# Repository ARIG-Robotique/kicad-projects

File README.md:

# Projets KiCAD de l'association ARIG

 ## Alimentation
 
 ### MasterAlim
 
 Module de contrôle I2C des alimentations et AU logique.

 ### ModuleAlim3A
 
 Module d'alimentation régulée 3A.

 ### ModuleAlim6A
 
 Module d'alimentation régulée 6A.

 ### ModuleMesure
 
 Module I2C de mesure tension/courant, 4 mesures.
 
 ### ModuleMesureDemi
 
 Module I2C de mesure tension/courant, 2 mesures.

 ## CapteursNumerique
 
 Module de lecture de 8 capteurs tout ou rien sur I2C.

 ## ControleursPompes
 
 Controle I2C de 4 pompes à vide + electrovannes + presiostats.

 ## InterfaceRaspi
 
 Shield Raspberry Pi pour connecter les modules.

 ## MultiplexeurCouleur
 
 Module de multiplexage I2C pour 8 capteurs de couleur.

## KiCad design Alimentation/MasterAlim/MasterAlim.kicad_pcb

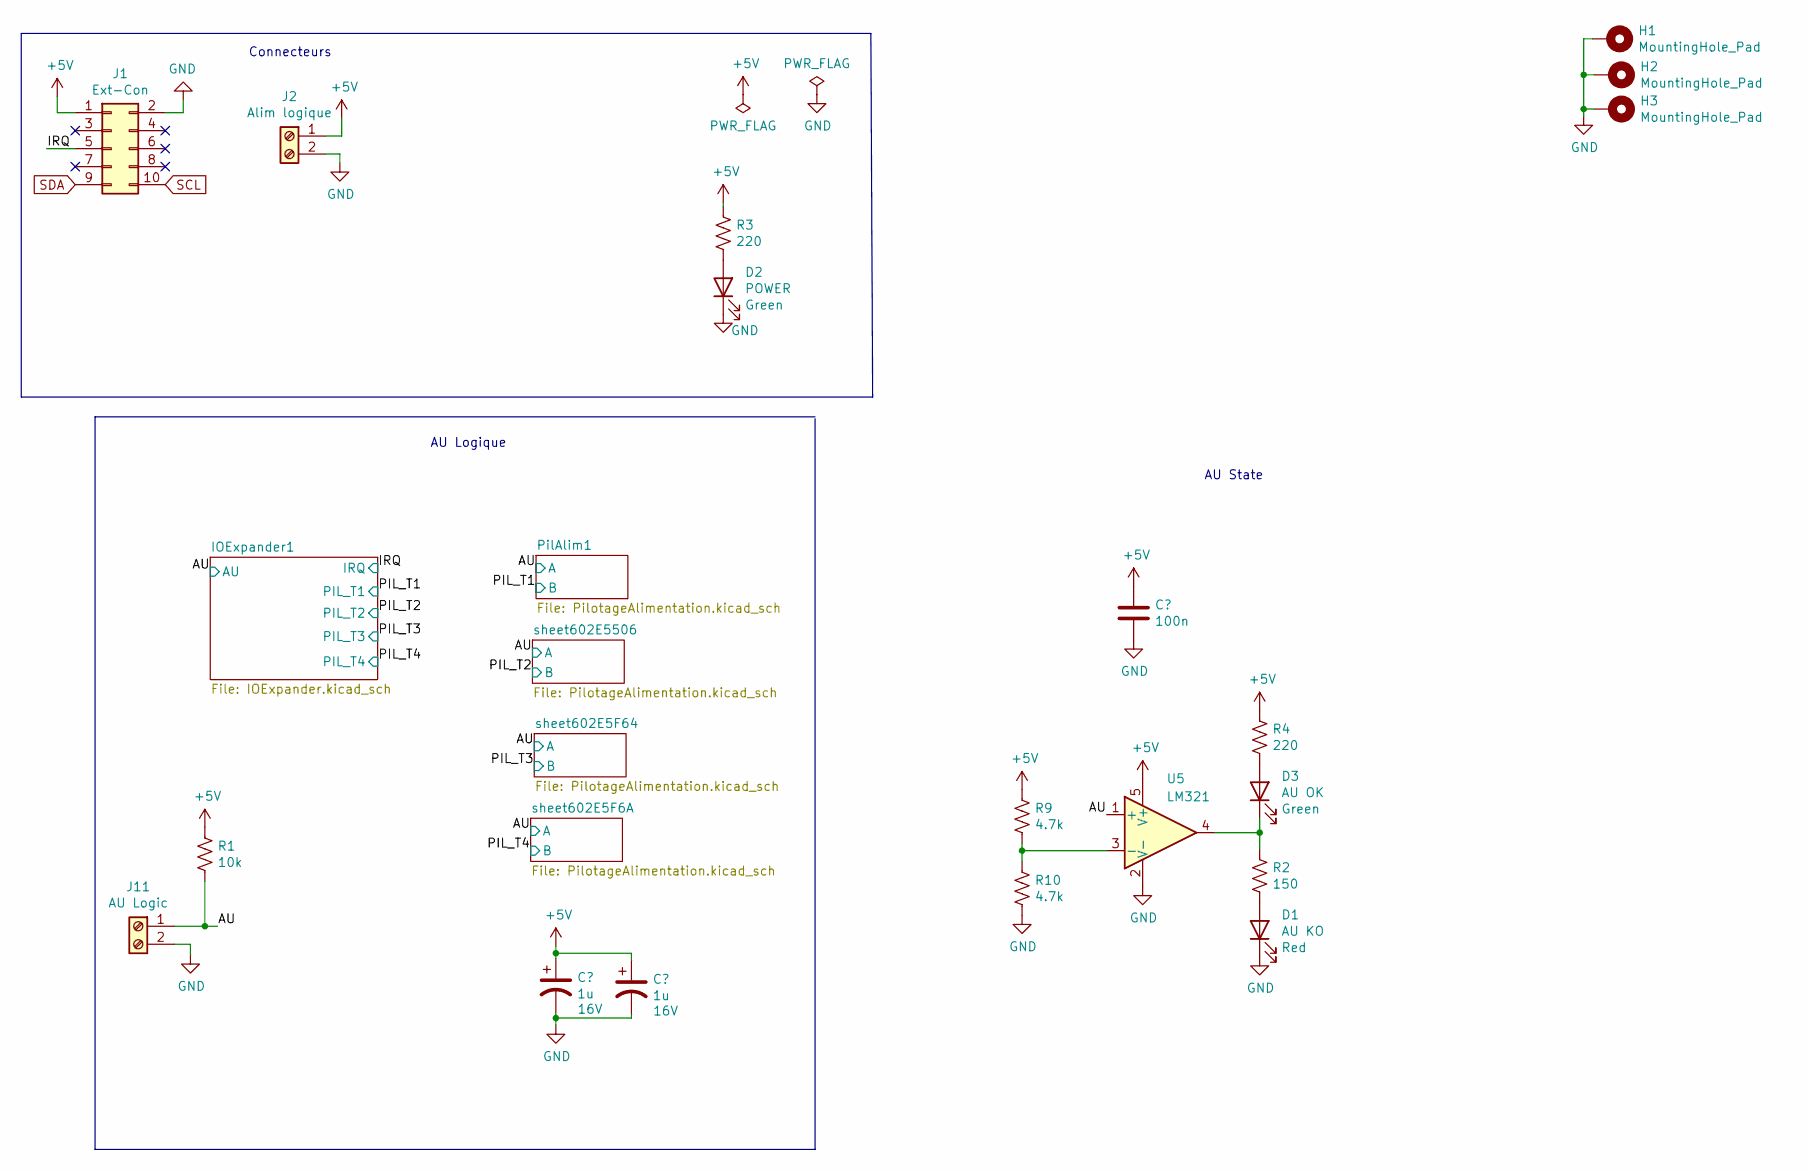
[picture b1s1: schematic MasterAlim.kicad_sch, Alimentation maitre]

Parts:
C1, C3: 1u; CP_Radial_D5.0mm_P2.50mm; JLCPCB BOM 0
C4: 100n; C_0603_1608Metric_Pad1.08x0.95mm_HandSolder; LCSC Part C14663
D1: AU KO; LED_0805_2012Metric; LCSC Part C72037
D2: POWER; LED_0805_2012Metric; LCSC Part C63855
D3: AU OK; LED_0805_2012Metric; LCSC Part C63855
H1, H2, H3: MountingHole_Pad; MountingHole_3.2mm_M3_Pad_Via; JLCPCB BOM 0
J1: Ext-Con; IDC-Header_2x05_P2.54mm_Vertical; JLCPCB BOM 0
J2: Alim logique; TerminalBlock_Phoenix_MKDS-1,5-2-5.08_1x02_P5.08mm_Horizont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; JLCPCB BOM 0
J11: AU Logic; TerminalBlock_Phoenix_MPT-0,5-2-2.54_1x02_P2.54mm_Horizontal; JLCPCB BOM 0
R1: 10k; R_0805_2012Metric_Pad1.20x1.40mm_HandSolder; LCSC Part C17414
R2: 150; R_0805_2012Metric_Pad1.20x1.40mm_HandSolder; LCSC Part C17471
R3, R4: 220; R_0805_2012Metric_Pad1.20x1.40mm_HandSolder; LCSC Part C17557
R9, R10: 4.7k; R_0805_2012Metric_Pad1.20x1.40mm_HandSolder
U5: LM321; SOT-23-5

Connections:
+5V: C1.1, C3.1, C4.1, J1.1, J2.1, R1.1, R3.1, R4.1, R9.1, U5.5 (V+); also elsewhere on the board
/AU: J11.1, R1.2, U5.1 (+); also elsewhere on the board
/IRQ: J1.5; also elsewhere on the board
GND: C1.2, C3.2, C4.2, D1.1 (K), D2.1 (K), H1.1, H2.1, H3.1, J1.2, J2.2, J11.2, R10.2, U5.2 (V-); also elsewhere on the board
unnamed: D1.2 (A), R2.2
unnamed: D2.2 (A), R3.2
unnamed: D3.1 (K), R2.1, U5.4
unnamed: D3.2 (A), R4.2
unnamed: R9.2, R10.1, U5.3 (-)
SCL: J1.10; also elsewhere on the board
SDA: J1.9; also elsewhere on the board

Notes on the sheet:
Connecteurs
AU Logique
AU State

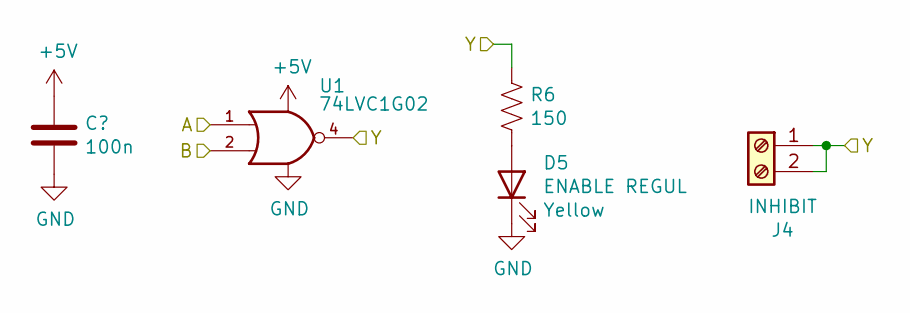
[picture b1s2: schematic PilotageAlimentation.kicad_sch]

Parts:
C6: 100n; C_0603_1608Metric_Pad1.08x0.95mm_HandSolder; LCSC Part C14663
D5: ENABLE REGUL; LED_0805_2012Metric; LCSC Part C74346
J4: INHIBIT; TerminalBlock_Phoenix_MPT-0,5-2-2.54_1x02_P2.54mm_Horizontal; JLCPCB BOM 0
R6: 150; R_0805_2012Metric_Pad1.20x1.40mm_HandSolder; LCSC Part C17471
U1: 74LVC1G02; SOT-23-5_HandSoldering; LCSC Part C16360

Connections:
+5V: C6.1, U1.5 (VCC); also elsewhere on the board
/AU: U1.1; also elsewhere on the board
/PIL_T1: U1.2; also elsewhere on the board
GND: C6.2, D5.1 (K), U1.3 (GND); also elsewhere on the board
unnamed: D5.2 (A), R6.2

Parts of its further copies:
C2, C8, C10: 100n; C_0603_1608Metric_Pad1.08x0.95mm_HandSolder; LCSC Part C14663
D4, D6, D8: ENABLE REGUL; LED_0805_2012Metric; LCSC Part C74346
J6, J8, J12: INHIBIT; TerminalBlock_Phoenix_MPT-0,5-2-2.54_1x02_P2.54mm_Horizontal; JLCPCB BOM 0
R5, R7, R8: 150; R_0805_2012Metric_Pad1.20x1.40mm_HandSolder; LCSC Part C17471
U2, U3, U4: 74LVC1G02; SOT-23-5_HandSoldering; LCSC Part C16360

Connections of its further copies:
+5V: C2.1, C8.1, C10.1, U2.5 (VCC), U3.5 (VCC), U4.5 (VCC); also elsewhere on the board
/AU: U2.1, U3.1, U4.1; also elsewhere on the board
/PIL_T2: U2.2; also elsewhere on the board
/PIL_T3: U3.2; also elsewhere on the board
/PIL_T4: U4.2; also elsewhere on the board
/sheet602E5F6A/Y: J12.1, J12.2, R8.1, U4.4
/sheet602E5F64/Y: J8.1, J8.2, R7.1, U3.4
GND: C2.2, C8.2, C10.2, D4.1 (K), D6.1 (K), D8.1 (K), U2.3 (GND), U3.3 (GND), U4.3 (GND); also elsewhere on the board
unnamed: D4.2 (A), R5.2
unnamed: D6.2 (A), R7.2
unnamed: D8.2 (A), R8.2

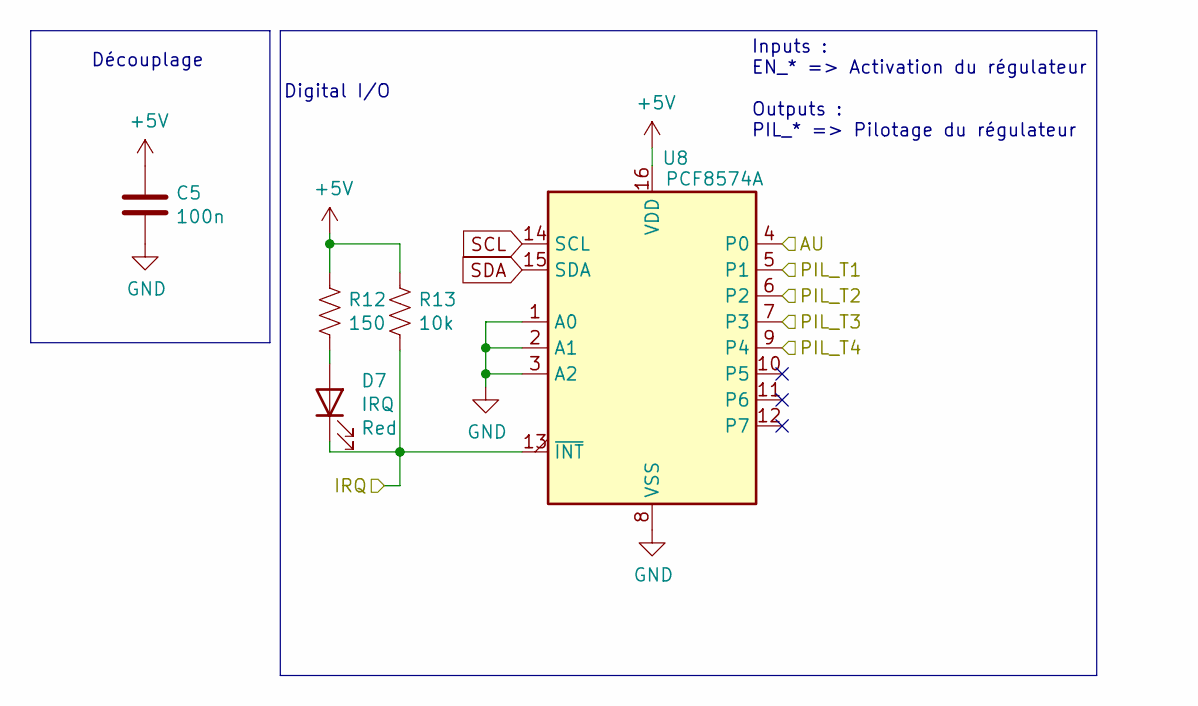
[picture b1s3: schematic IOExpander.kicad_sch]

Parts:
C5: 100n; C_0603_1608Metric_Pad1.08x0.95mm_HandSolder; LCSC Part C14663
D7: IRQ; LED_0805_2012Metric; LCSC Part C72037
R12: 150; R_0805_2012Metric_Pad1.20x1.40mm_HandSolder; LCSC Part C17471
R13: 10k; R_0805_2012Metric_Pad1.20x1.40mm_HandSolder; LCSC Part C17414
U8: PCF8574A; SOIC-16W_7.5x10.3mm_P1.27mm; LCSC Part C86832

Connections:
+5V: C5.1, R12.1, R13.1, U8.16 (VDD); also elsewhere on the board
/AU: U8.4 (P0); also elsewhere on the board
/IRQ: D7.1 (K), R13.2, U8.13 (~INT); also elsewhere on the board
/PIL_T1: U8.5 (P1); also elsewhere on the board
/PIL_T2: U8.6 (P2); also elsewhere on the board
/PIL_T3: U8.7 (P3); also elsewhere on the board
/PIL_T4: U8.9 (P4); also elsewhere on the board
GND: C5.2, U8.1 (A0), U8.2 (A1), U8.3 (A2), U8.8 (VSS); also elsewhere on the board
unnamed: D7.2 (A), R12.2
SCL: U8.14 (SCL); also elsewhere on the board
SDA: U8.15 (SDA); also elsewhere on the board

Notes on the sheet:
Digital I/O
Inputs : EN_* => Activation du régulateur Outputs : PIL_* => Pilotage du régulateur
Découplage

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
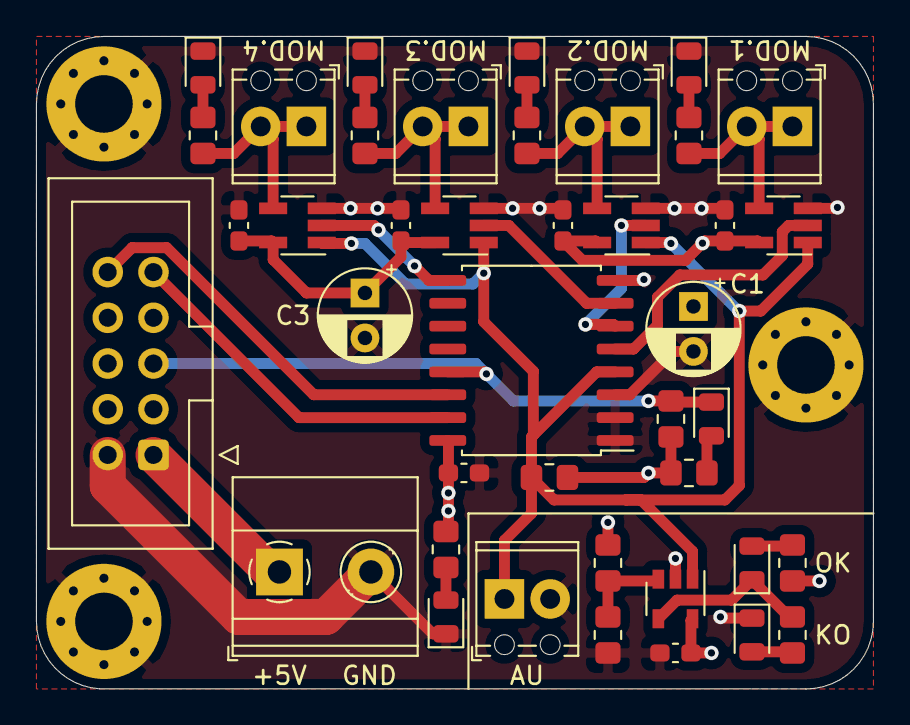
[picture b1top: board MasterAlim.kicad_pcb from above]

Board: 4 copper layers, 46.5 x 36.2 mm, 44 parts (0 on the bottom side), 24 nets.

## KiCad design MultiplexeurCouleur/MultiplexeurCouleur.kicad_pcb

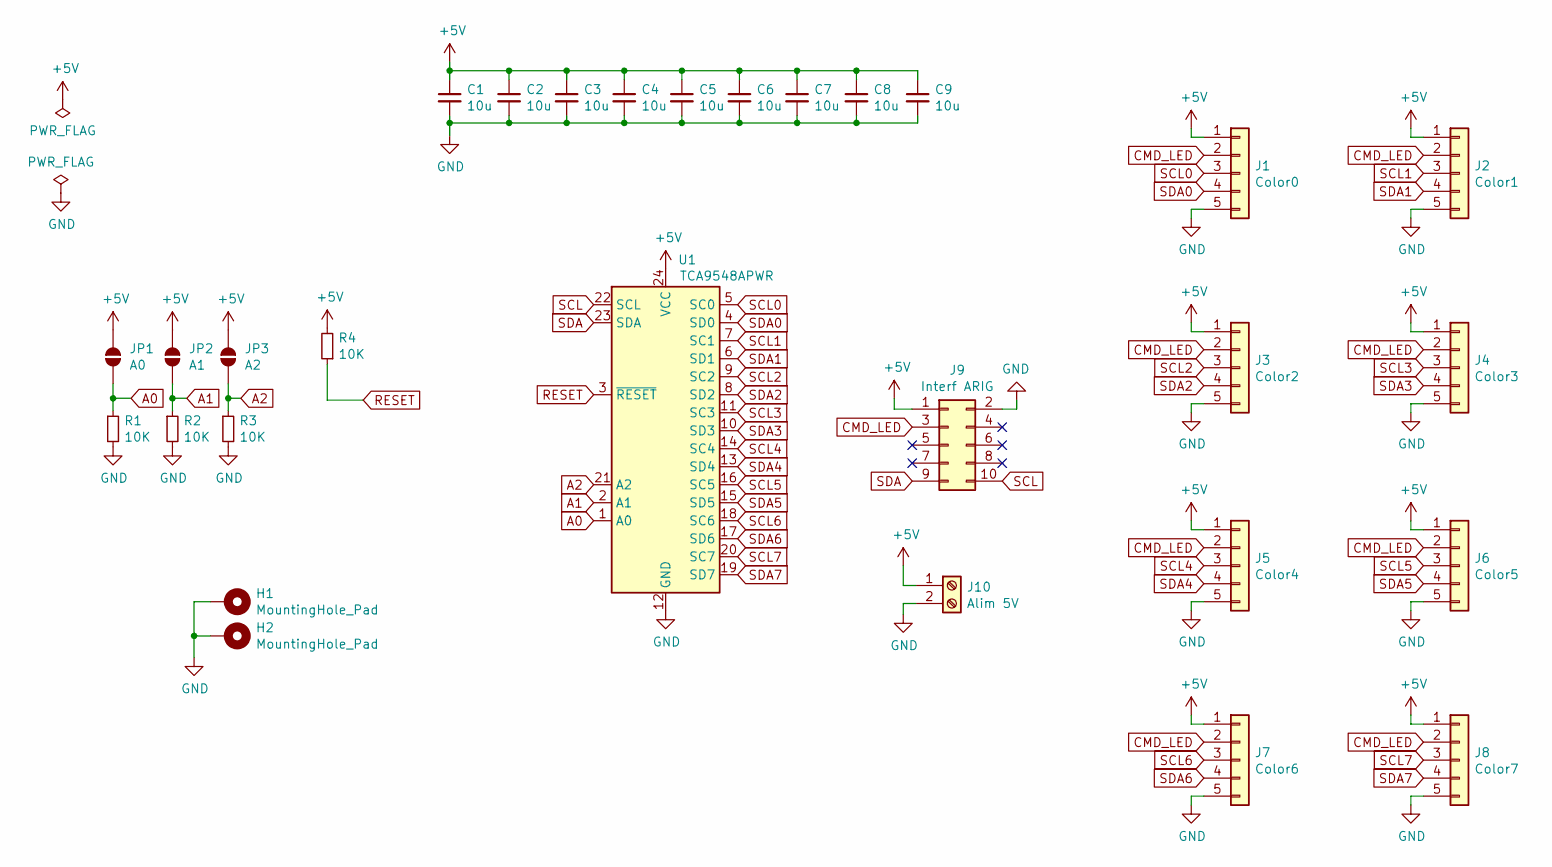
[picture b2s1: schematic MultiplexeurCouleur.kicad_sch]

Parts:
C1, C2, C3, C4, C5, C6, C7, C8, C9: 10u; C_0805_2012Metric_Pad1.18x1.45mm_HandSolder; LCSC Part C15850
H1, H2: MountingHole_Pad; MountingHole_3.2mm_M3_Pad_Via; JLCPCB BOM 0
J1: Color0; JST_PH_B5B-PH-K_1x05_P2.00mm_Vertical; JLCPCB BOM 0
J2: Color1; JST_PH_B5B-PH-K_1x05_P2.00mm_Vertical; JLCPCB BOM 0
J3: Color2; JST_PH_B5B-PH-K_1x05_P2.00mm_Vertical; JLCPCB BOM 0
J4: Color3; JST_PH_B5B-PH-K_1x05_P2.00mm_Vertical; JLCPCB BOM 0
J5: Color4; JST_PH_B5B-PH-K_1x05_P2.00mm_Vertical; JLCPCB BOM 0
J6: Color5; JST_PH_B5B-PH-K_1x05_P2.00mm_Vertical; JLCPCB BOM 0
J7: Color6; JST_PH_B5B-PH-K_1x05_P2.00mm_Vertical; JLCPCB BOM 0
J8: Color7; JST_PH_B5B-PH-K_1x05_P2.00mm_Vertical; JLCPCB BOM 0
J9: Interf ARIG; IDC-Header_2x05_P2.54mm_Vertical; JLCPCB BOM 0
J10: Alim 5V; TerminalBlock_Phoenix_MPT-0,5-2-2.54_1x02_P2.54mm_Horizontal; JLCPCB BOM 0
JP1: A0; SolderJumper-2_P1.3mm_Open_Pad1.0x1.5mm; JLCPCB BOM 0
JP2: A1; SolderJumper-2_P1.3mm_Open_Pad1.0x1.5mm; JLCPCB BOM 0
JP3: A2; SolderJumper-2_P1.3mm_Open_Pad1.0x1.5mm; JLCPCB BOM 0
R1, R2, R3, R4: 10K; R_0805_2012Metric_Pad1.20x1.40mm_HandSolder; LCSC Part C17414
U1: TCA9548APWR; TSSOP-24_4.4x7.8mm_P0.65mm; LCSC Part C130026

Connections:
+5V: C1.1, C2.1, C3.1, C4.1, C5.1, C6.1, C7.1, C8.1, C9.1, J1.1, J2.1, J3.1, J4.1, J5.1, J6.1, J7.1, J8.1, J9.1, J10.1, JP1.2 (B), JP2.2 (B), JP3.2 (B), R4.2, U1.24 (VCC)
A0: JP1.1 (A), R1.1, U1.1 (A0)
A1: JP2.1 (A), R2.1, U1.2 (A1)
A2: JP3.1 (A), R3.1, U1.21 (A2)
CMD_LED: J1.2, J2.2, J3.2, J4.2, J5.2, J6.2, J7.2, J8.2, J9.3
GND: C1.2, C2.2, C3.2, C4.2, C5.2, C6.2, C7.2, C8.2, C9.2, H1.1, H2.1, J1.5, J2.5, J3.5, J4.5, J5.5, J6.5, J7.5, J8.5, J9.2, J10.2, R1.2, R2.2, R3.2, U1.12 (GND)
RESET: R4.1, U1.3 (~RESET)
SCL: J9.10, U1.22 (SCL)
SCL0: J1.3, U1.5 (SC0)
SCL1: J2.3, U1.7 (SC1)
SCL2: J3.3, U1.9 (SC2)
SCL3: J4.3, U1.11 (SC3)
SCL4: J5.3, U1.14 (SC4)
SCL5: J6.3, U1.16 (SC5)
SCL6: J7.3, U1.18 (SC6)
SCL7: J8.3, U1.20 (SC7)
SDA: J9.9, U1.23 (SDA)
SDA0: J1.4, U1.4 (SD0)
SDA1: J2.4, U1.6 (SD1)
SDA2: J3.4, U1.8 (SD2)
SDA3: J4.4, U1.10 (SD3)
SDA4: J5.4, U1.13 (SD4)
SDA5: J6.4, U1.15 (SD5)
SDA6: J7.4, U1.17 (SD6)
SDA7: J8.4, U1.19 (SD7)

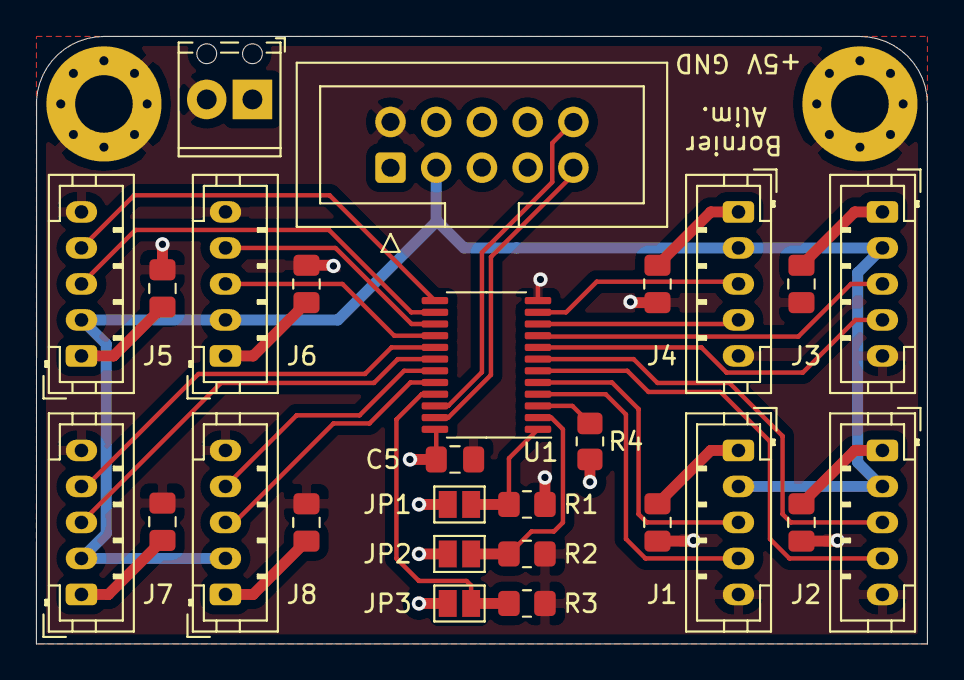
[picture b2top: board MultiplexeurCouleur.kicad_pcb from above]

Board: 4 copper layers, 49.5 x 33.8 mm, 29 parts (0 on the bottom side), 25 nets.

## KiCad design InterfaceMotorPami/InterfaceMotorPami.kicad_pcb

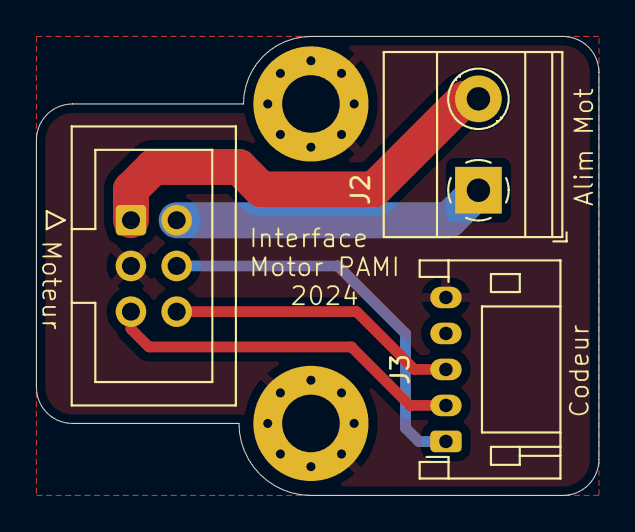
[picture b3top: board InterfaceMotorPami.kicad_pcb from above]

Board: 2 copper layers, 31.3 x 25.5 mm, 5 parts (0 on the bottom side), 6 nets.

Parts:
H1, H2: MountingHole_Pad; MountingHole_3.2mm_M3_Pad_Via
J1: MOT; IDC-Header_2x03_P2.54mm_Vertical
J2: PONT H; TerminalBlock_Phoenix_MKDS-1,5-2-5.08_1x02_P5.08mm_Horizont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
J3: Codeur; JST_PH_S5B-PH-K_1x05_P2.00mm_Horizontal

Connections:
+5V: J1.4, J3.1
/CHA: J1.5, J3.2
/CHB: J1.6, J3.3
/MOT+: J1.2, J2.1
/MOT-: J1.1, J2.2
GND: H1.1, H2.1, J1.3, J3.5

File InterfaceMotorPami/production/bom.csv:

Designator,Footprint,Quantity,Value,LCSC Part #
"H1, H2",MountingHole_3.2mm_M3_Pad_Via,2,MountingHole_Pad,
J1,IDC-Header_2x03_P2.54mm_Vertical,1,MOT,
J2,"TerminalBlock_Phoenix_MKDS-1,5-2-5.08_1x02_P5.08mm_Horizontal",1,PONT H,
J3,JST_PH_S5B-PH-K_1x05_P2.00mm_Horizontal,1,Codeur,

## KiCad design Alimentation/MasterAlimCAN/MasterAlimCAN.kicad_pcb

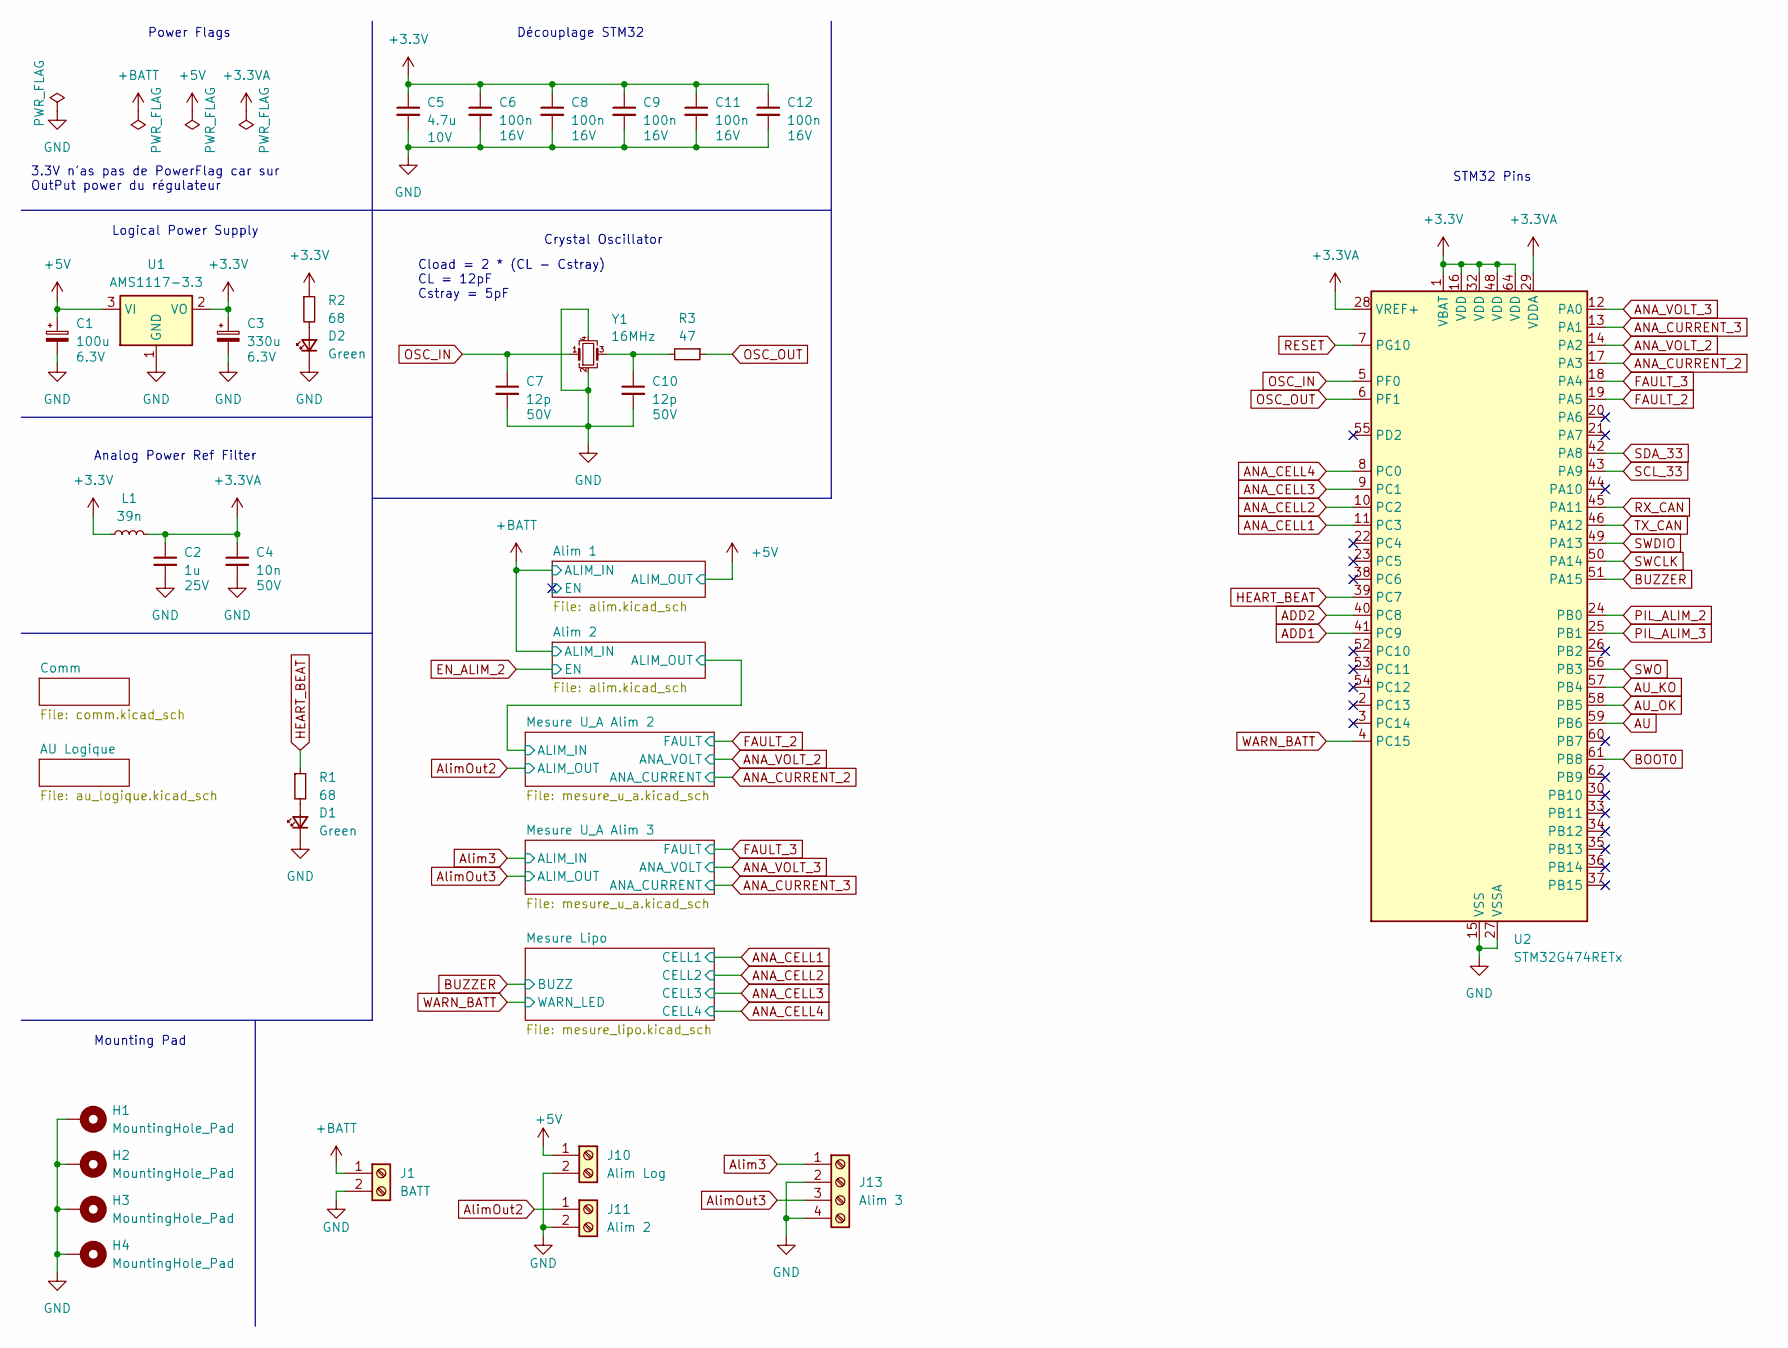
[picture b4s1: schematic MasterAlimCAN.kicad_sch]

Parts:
C1: 100u; CP_Elec_5x5.3; LCSC Part C249463
C2: 1u; C_0402_1005Metric_Pad0.74x0.62mm_HandSolder; LCSC Part C52923
C3: 330u; CP_Elec_6.3x7.7; LCSC Part C249900
C4: 10n; C_0402_1005Metric_Pad0.74x0.62mm_HandSolder; LCSC Part C15195
C5: 4.7u; C_0402_1005Metric_Pad0.74x0.62mm_HandSolder; LCSC Part C23733
C6, C8, C9, C11, C12: 100n; C_0402_1005Metric_Pad0.74x0.62mm_HandSolder; LCSC Part C1525
C7, C10: 12p; C_0402_1005Metric_Pad0.74x0.62mm_HandSolder; LCSC Part C1547
D1, D2: Green; LED_0805_2012Metric_Pad1.15x1.40mm_HandSolder; LCSC Part C63855
H1, H2, H3, H4: MountingHole_Pad; MountingHole_3.2mm_M3_Pad_Via; JLCPCB BOM 0
J1: BATT; TerminalBlock_Phoenix_MKDS-1,5-2-5.08_1x02_P5.08mm_Horizont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; JLCPCB BOM 0
J10: Alim Log; TerminalBlock_Phoenix_MKDS-1,5-2-5.08_1x02_P5.08mm_Horizont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; JLCPCB BOM 0
J11: Alim 2; TerminalBlock_Phoenix_MKDS-1,5-2-5.08_1x02_P5.08mm_Horizont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; JLCPCB BOM 0
J13: Alim 3; TerminalBlock_Phoenix_MKDS-1,5-4-5.08_1x04_P5.08mm_Horizont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; JLCPCB BOM 0
L1: 39n; L_0402_1005Metric_Pad0.77x0.64mm_HandSolder; LCSC Part C26443
R1, R2: 68; R_0805_2012Metric_Pad1.20x1.40mm_HandSolder; LCSC Part C17802
R3: 47; R_0402_1005Metric_Pad0.72x0.64mm_HandSolder; LCSC Part C25118
U1: AMS1117-3.3; SOT-223-3_TabPin2; LCSC Part C6186
U2: STM32G474RETx; LQFP-64_10x10mm_P0.5mm; LCSC Part C521608
Y1: 16MHz; Crystal_SMD_3225-4Pin_3.2x2.5mm_HandSoldering; LCSC Part C13738

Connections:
+3.3V: C3.1, C5.1, C6.1, C8.1, C9.1, C11.1, C12.1, L1.1, R2.1, U1.2 (VO), U2.1 (VBAT), U2.16 (VDD), U2.32 (VDD), U2.48 (VDD), U2.64 (VDD); also elsewhere on the board
+3.3VA: C2.1, C4.1, L1.2, U2.28 (VREF+), U2.29 (VDDA)
+5V: C1.1, J10.1, U1.3 (VI); also elsewhere on the board
+BATT: J1.1; also elsewhere on the board
ADD1: U2.41 (PC9); also elsewhere on the board
ADD2: U2.40 (PC8); also elsewhere on the board
ANA_CELL1: U2.11 (PC3); also elsewhere on the board
ANA_CELL2: U2.10 (PC2); also elsewhere on the board
ANA_CELL3: U2.9 (PC1); also elsewhere on the board
ANA_CELL4: U2.8 (PC0); also elsewhere on the board
ANA_CURRENT_2: U2.17 (PA3); also elsewhere on the board
ANA_CURRENT_3: U2.13 (PA1); also elsewhere on the board
ANA_VOLT_2: U2.14 (PA2); also elsewhere on the board
ANA_VOLT_3: U2.12 (PA0); also elsewhere on the board
AU: U2.59 (PB6); also elsewhere on the board
AU_KO: U2.57 (PB4); also elsewhere on the board
AU_OK: U2.58 (PB5); also elsewhere on the board
AlimOut2: J11.1; also elsewhere on the board
AlimOut3: J13.3; also elsewhere on the board
BOOT0: U2.61 (PB8); also elsewhere on the board
BUZZER: U2.51 (PA15); also elsewhere on the board
GND: C1.2, C2.2, C3.2, C4.2, C5.2, C6.2, C7.2, C8.2, C9.2, C10.2, C11.2, C12.2, D1.1 (K), D2.1 (K), H1.1, H2.1, H3.1, H4.1, J1.2, J10.2, J11.2, J13.2, J13.4, U1.1 (GND), U2.15 (VSS), U2.27 (VSSA), U2.31 (VSS), U2.47 (VSS), U2.63 (VSS), Y1.2, Y1.4; also elsewhere on the board
HEART_BEAT: R1.1, U2.39 (PC7)
unnamed: C10.1, R3.2, Y1.3
unnamed: D1.2 (A), R1.2
unnamed: D2.2 (A), R2.2
OSC_IN: C7.1, U2.5 (PF0), Y1.1
OSC_OUT: R3.1, U2.6 (PF1)
PIL_ALIM_2: U2.24 (PB0); also elsewhere on the board
PIL_ALIM_3: U2.25 (PB1); also elsewhere on the board
RESET: U2.7 (PG10); also elsewhere on the board
RX_CAN: U2.45 (PA11); also elsewhere on the board
SCL_33: U2.43 (PA9); also elsewhere on the board
SDA_33: U2.42 (PA8); also elsewhere on the board
SWCLK: U2.50 (PA14); also elsewhere on the board
SWDIO: U2.49 (PA13); also elsewhere on the board
SWO: U2.56 (PB3); also elsewhere on the board
TX_CAN: U2.46 (PA12); also elsewhere on the board
WARN_BATT: U2.4 (PC15); also elsewhere on the board

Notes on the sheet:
Analog Power Ref Filter
STM32 Pins
Mounting Pad
Crystal Oscillator
3.3V n'as pas de PowerFlag car sur OutPut power du régulateur
Découplage STM32
Power Flags
Logical Power Supply
Cload = 2 * (CL - Cstray) CL = 12pF Cstray = 5pF

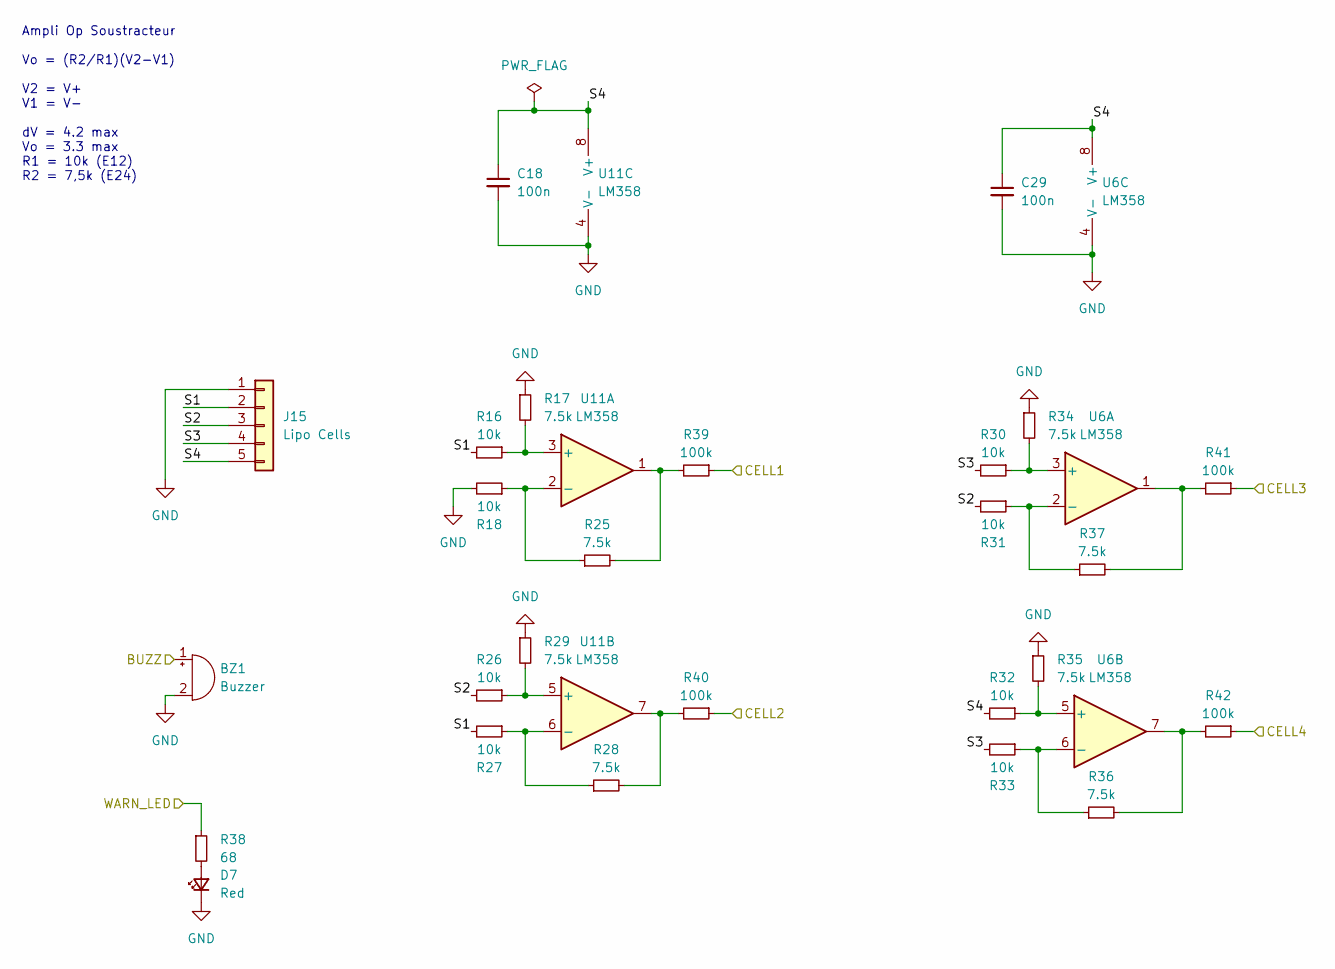
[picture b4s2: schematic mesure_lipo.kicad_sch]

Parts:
BZ1: Buzzer; MagneticBuzzer_CUI_CST-931RP-A; JLCPCB BOM 0
C18, C29: 100n; C_0402_1005Metric_Pad0.74x0.62mm_HandSolder; LCSC Part C100072
D7: Red; LED_0805_2012Metric_Pad1.15x1.40mm_HandSolder; LCSC Part C72037
J15: Lipo Cells; JST_PH_S5B-PH-K_1x05_P2.00mm_Horizontal; JLCPCB BOM 0
R16, R18, R26, R27, R30, R31, R32, R33: 10k; R_0805_2012Metric_Pad1.20x1.40mm_HandSolder; LCSC Part C17414
R17, R25, R28, R29, R34, R35, R36, R37: 7.5k; R_0805_2012Metric_Pad1.20x1.40mm_HandSolder; LCSC Part C17807
R38: 68; R_0805_2012Metric_Pad1.20x1.40mm_HandSolder; LCSC Part C17802
R39, R40, R41, R42: 100k; R_0805_2012Metric_Pad1.20x1.40mm_HandSolder; LCSC Part C25611
U6, U11: LM358; SO-8_3.9x4.9mm_P1.27mm; LCSC Part C9418

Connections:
/Mesure Lipo/S1: J15.2, R16.2, R27.2
/Mesure Lipo/S2: J15.3, R26.2, R31.2
/Mesure Lipo/S3: J15.4, R30.2, R33.2
/Mesure Lipo/S4: C18.1, C29.1, J15.5, R32.2, U6.8 (V+), U11.8 (V+)
ANA_CELL1: R39.1; also elsewhere on the board
ANA_CELL2: R40.1; also elsewhere on the board
ANA_CELL3: R41.1; also elsewhere on the board
ANA_CELL4: R42.1; also elsewhere on the board
BUZZER: BZ1.1 (+); also elsewhere on the board
GND: BZ1.2 (-), C18.2, C29.2, D7.1 (K), J15.1, R17.1, R18.2, R29.1, R34.1, R35.1, U6.4 (V-), U11.4 (V-); also elsewhere on the board
unnamed: D7.2 (A), R38.2
unnamed: R25.2, R39.2, U11.1
unnamed: R28.2, R40.2, U11.7
unnamed: R36.2, R42.2, U6.7
unnamed: R37.2, R41.2, U6.1
unnamed: R30.1, R34.2, U6.3 (+)
unnamed: R31.1, R37.1, U6.2 (-)
unnamed: R32.1, R35.2, U6.5 (+)
unnamed: R33.1, R36.1, U6.6 (-)
unnamed: R16.1, R17.2, U11.3 (+)
unnamed: R18.1, R25.1, U11.2 (-)
unnamed: R26.1, R29.2, U11.5 (+)
unnamed: R27.1, R28.1, U11.6 (-)
WARN_BATT: R38.1; also elsewhere on the board

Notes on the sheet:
Ampli Op Soustracteur Vo = (R2/R1)(V2-V1) V2 = V+ V1 = V- dV = 4.2 max Vo = 3.3 max R1 = 10k (E12) R2 = 7,5k (E24)

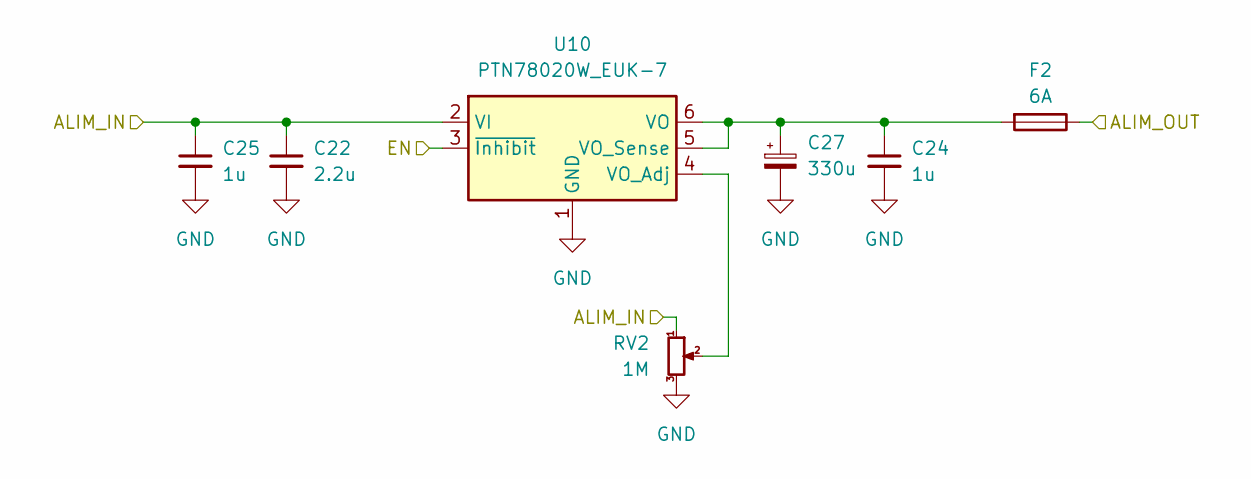
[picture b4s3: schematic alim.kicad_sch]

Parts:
C22: 2.2u; C_1206_3216Metric_Pad1.33x1.80mm_HandSolder; LCSC Part C50254
C24: 1u; C_0402_1005Metric_Pad0.74x0.62mm_HandSolder; LCSC Part C52923
C25: 1u; C_0805_2012Metric_Pad1.18x1.45mm_HandSolder; LCSC Part C28323
C27: 330u; CP_Elec_8x10; LCSC Part C134842
F2: 6A; Fuseholder_Cylinder-5x20mm_Schurter_0031_8201_Horizontal_Op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; JLCPCB BOM 0
RV2: 1M; Potentiometer_Bourns_3266Y_Vertical; JLCPCB BOM 0
U10: PTN78020W_EUK-7; Texas_EUK_R-PDSS-T7_THT; LCSC Part C5219636

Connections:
+BATT: C22.1, C25.1, RV2.1, U10.2 (VI); also elsewhere on the board
EN_ALIM_2: U10.3 (~Inhibit); also elsewhere on the board
GND: C22.2, C24.2, C25.2, C27.2, RV2.3, U10.1 (GND), U10.7 (GND); also elsewhere on the board
unnamed: RV2.2, U10.4 (VO_Adj)

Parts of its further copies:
C21: 1u; C_0805_2012Metric_Pad1.18x1.45mm_HandSolder; LCSC Part C28323
C23: 330u; CP_Elec_8x10; LCSC Part C134842
C26: 2.2u; C_1206_3216Metric_Pad1.33x1.80mm_HandSolder; LCSC Part C50254
C28: 1u; C_0402_1005Metric_Pad0.74x0.62mm_HandSolder; LCSC Part C52923
F1: 6A; Fuseholder_Cylinder-5x20mm_Schurter_0031_8201_Horizontal_Op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; JLCPCB BOM 0
RV1: 1M; Potentiometer_Bourns_3266Y_Vertical; JLCPCB BOM 0
U9: PTN78020W_EUK-7; Texas_EUK_R-PDSS-T7_THT; LCSC Part C5219636

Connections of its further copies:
+5V: F1.1; also elsewhere on the board
+BATT: C21.1, C26.1, RV1.1, U9.2 (VI); also elsewhere on the board
/Alim 1/EN: U9.3 (~Inhibit)
GND: C21.2, C23.2, C26.2, C28.2, RV1.3, U9.1 (GND), U9.7 (GND); also elsewhere on the board
unnamed: RV1.2, U9.4 (VO_Adj)

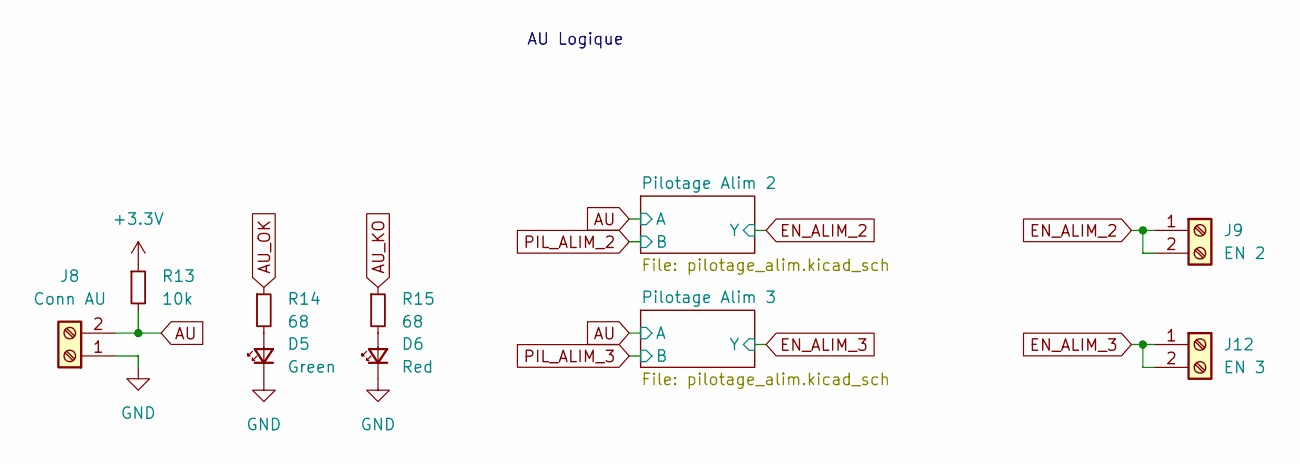
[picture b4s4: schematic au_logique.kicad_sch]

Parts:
D5: Green; LED_0805_2012Metric_Pad1.15x1.40mm_HandSolder; LCSC Part C63855
D6: Red; LED_0805_2012Metric_Pad1.15x1.40mm_HandSolder; LCSC Part C72037
J8: Conn AU; TerminalBlock_Phoenix_MPT-0,5-2-2.54_1x02_P2.54mm_Horizontal; JLCPCB BOM 0
J9: EN 2; TerminalBlock_Phoenix_MPT-0,5-2-2.54_1x02_P2.54mm_Horizontal; JLCPCB BOM 0
J12: EN 3; TerminalBlock_Phoenix_MPT-0,5-2-2.54_1x02_P2.54mm_Horizontal; JLCPCB BOM 0
R13: 10k; R_0805_2012Metric_Pad1.20x1.40mm_HandSolder; LCSC Part C17414
R14, R15: 68; R_0805_2012Metric_Pad1.20x1.40mm_HandSolder; LCSC Part C17802

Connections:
+3.3V: R13.1; also elsewhere on the board
AU: J8.2, R13.2; also elsewhere on the board
AU_KO: R15.1; also elsewhere on the board
AU_OK: R14.1; also elsewhere on the board
EN_ALIM_2: J9.1, J9.2; also elsewhere on the board
EN_ALIM_3: J12.1, J12.2; also elsewhere on the board
GND: D5.1 (K), D6.1 (K), J8.1; also elsewhere on the board
unnamed: D5.2 (A), R14.2
unnamed: D6.2 (A), R15.2

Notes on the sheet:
AU Logique

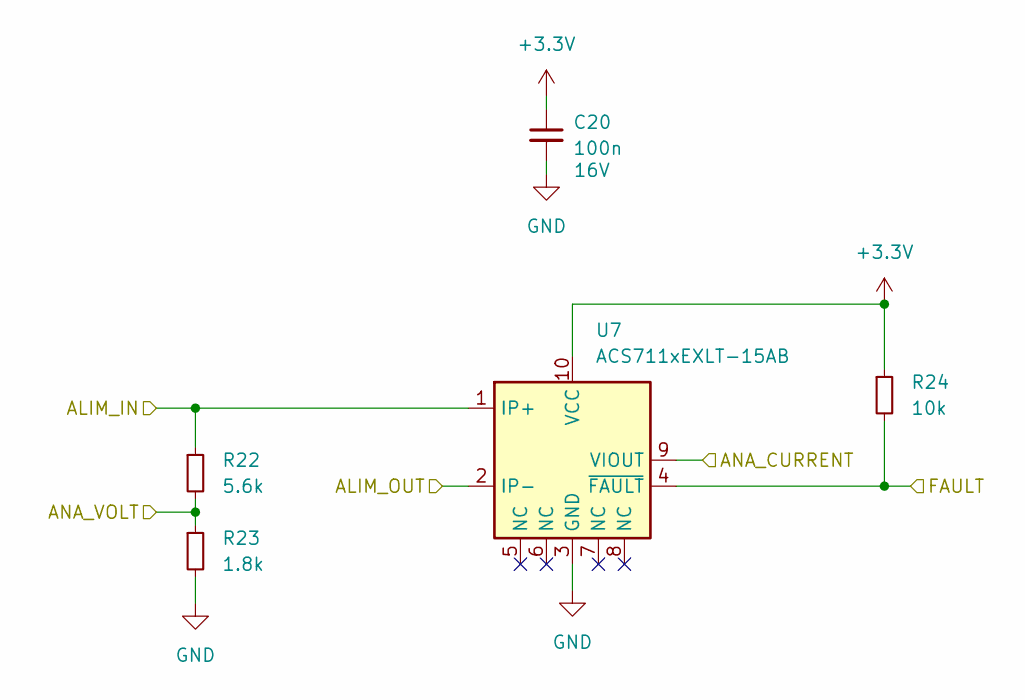
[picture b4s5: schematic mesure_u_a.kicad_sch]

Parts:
C20: 100n; C_0402_1005Metric_Pad0.74x0.62mm_HandSolder; LCSC Part C1525
R22: 5.6k; R_0805_2012Metric_Pad1.20x1.40mm_HandSolder; LCSC Part C26024
R23: 1.8k; R_0805_2012Metric_Pad1.20x1.40mm_HandSolder; LCSC Part C17398
R24: 10k; R_0805_2012Metric_Pad1.20x1.40mm_HandSolder; LCSC Part C17414
U7: ACS711xEXLT-15AB; Allegro_QFN-12-10-1EP_3x3mm_P0.5mm; LCSC Part C150824

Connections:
+3.3V: C20.1, R24.1, U7.10 (VCC); also elsewhere on the board
ANA_CURRENT_2: U7.9 (VIOUT); also elsewhere on the board
ANA_VOLT_3: R22.2, R23.1; also elsewhere on the board
AlimOut2: U7.2 (IP-); also elsewhere on the board
GND: C20.2, R23.2, U7.3 (GND); also elsewhere on the board

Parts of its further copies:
C19: 100n; C_0402_1005Metric_Pad0.74x0.62mm_HandSolder; LCSC Part C1525
R19: 5.6k; R_0805_2012Metric_Pad1.20x1.40mm_HandSolder; LCSC Part C26024
R20: 1.8k; R_0805_2012Metric_Pad1.20x1.40mm_HandSolder; LCSC Part C17398
R21: 10k; R_0805_2012Metric_Pad1.20x1.40mm_HandSolder; LCSC Part C17414
U8: ACS711xEXLT-15AB; Allegro_QFN-12-10-1EP_3x3mm_P0.5mm; LCSC Part C150824

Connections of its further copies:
+3.3V: C19.1, R21.1, U8.10 (VCC); also elsewhere on the board
ANA_CURRENT_3: U8.9 (VIOUT); also elsewhere on the board
ANA_VOLT_2: R19.2, R20.1; also elsewhere on the board
AlimOut3: U8.2 (IP-); also elsewhere on the board
GND: C19.2, R20.2, U8.3 (GND); also elsewhere on the board
